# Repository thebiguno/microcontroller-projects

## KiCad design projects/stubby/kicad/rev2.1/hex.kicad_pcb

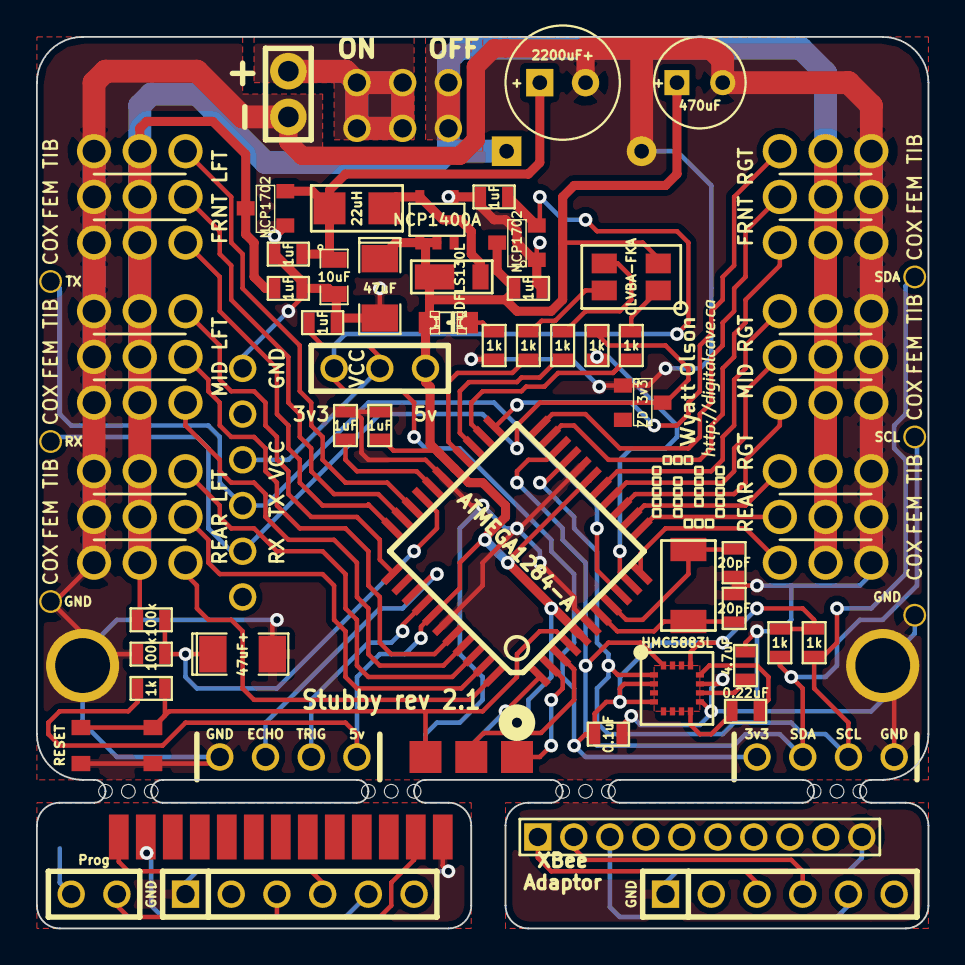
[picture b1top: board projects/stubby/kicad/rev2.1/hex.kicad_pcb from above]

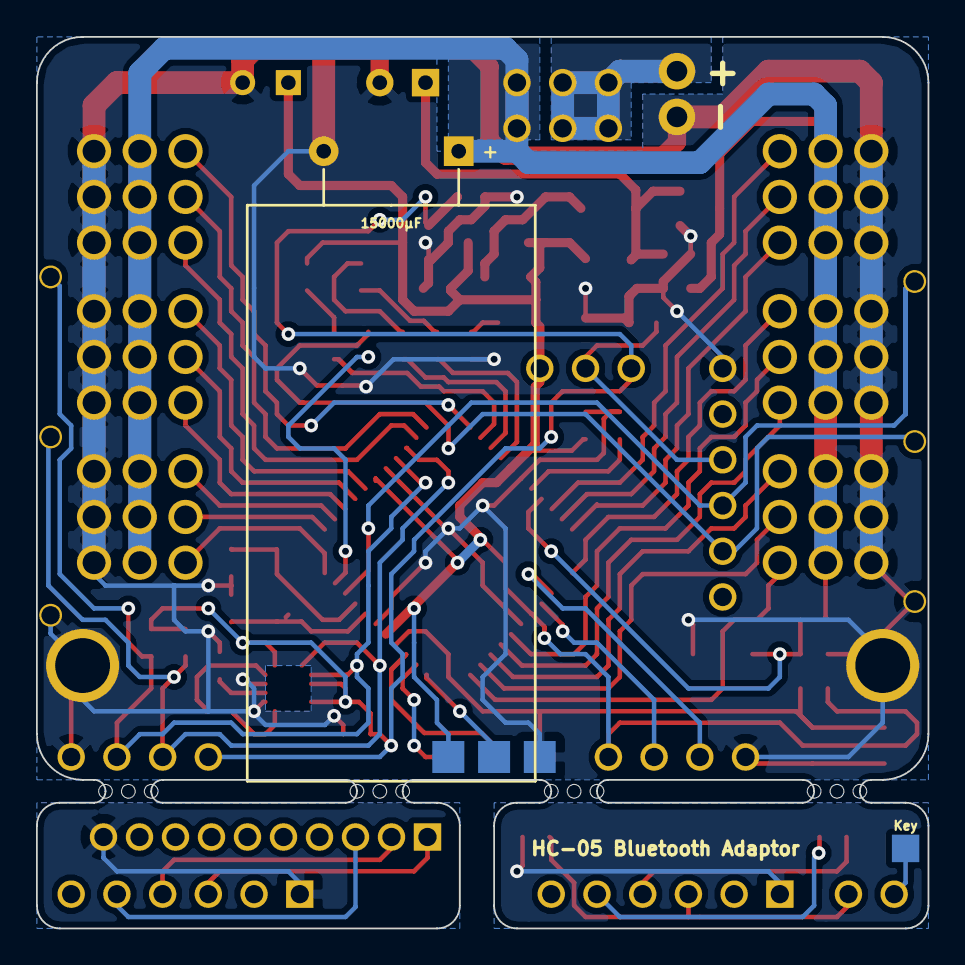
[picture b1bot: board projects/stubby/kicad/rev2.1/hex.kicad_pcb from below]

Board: 2 copper layers, 49.5 x 49.5 mm, 72 parts (2 on the bottom side), 60 nets.

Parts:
1PIN, 1PIN#2, 1PIN#3, 1PIN#4, 1PIN#5, 1PIN#6, 1PIN#7, 1PIN#8: P***; 1pin
C1: 10uF; SM0805
C2: 2200uF+; C1V7
C3, C4, C5, C12, C13, C14, C16: 1uF; SM0603_VALUE
C6: 4.7uF; SM0603_VALUE
C7, C8: 20pF; SM0603_VALUE
C9: 0.22uF; SM0603_VALUE
C10: 47uF; SM1206POL
C11: 470uF; C1V5
C15: 47uF+; SM1206POL
C17: 15000µF; C1V8
C19: 0.1uF; SM0603_VALUE
D1: DFLS130L; POWERDI_123
D2: LED; LED-0805-MARKED_ANODE
D3: CLVBA-FKA; 4-PLCC
IC1: ATMEGA1284-A; TQFP44
JP1: CONN_3; SIL-3
L1: 22uH; SM1007
P1, P2, P11: CONN_6; SIL-6
P3: CONN_10; SIL-10
P4: CONN_13; HC05_Edge
P5, P10: CONN_4; SIL-4
P6: CONN_2; SIL-2
P7: CONN_1; SIL-1
P8: BATT (4.8V-6V); SIL-2
P9: PROG; ISP_EDGE
R1, R2, R3, R4, R7, R8, R9, R10: 1k; SM0603_VALUE
R5, R6: 100k; SM0603_VALUE
S2: FRNT LFT; HEX_LEG
S3: FRNT RGT; HEX_LEG_REVERSE
S4: MID LFT; HEX_LEG
S5: MID RGT; HEX_LEG_REVERSE
S6: REAR LFT; HEX_LEG
S7: REAR RGT; HEX_LEG_REVERSE
SW1: SW_PUSH; sw_42_32
SW2: DPDT
U1: HMC5883L; LPCC-16
VAL: DIGITALCAVE_LOGO_WIDE_SMALL
VR1, VR3: MCP1702; SOT23
VR2: NCP1400A; SOT23-5
X1: CRYSTAL; CRYSTAL_SMD_5x3.2
ZD1: ZD 3v3; SOT23
mouse_bites: VAL**; mouse_bites
mouse_bites#2, mouse_bites#3, mouse_bites#4: VAL**; mouse_bites

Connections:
+3.3V: C13.1, C19.1, JP1.3, P5.1, R1.2, R2.2, U1.2, U1.4, U1.13, VR3.3
+5V: C10.1, C11.1, C12.2, C14.1, D1.2, D2.1, D3.2, IC1.5, IC1.17, IC1.27, IC1.38, JP1.1, P9.2, P10.1, R3.1, VR2.1, VR2.2, VR3.2
+BATT: C4.1, C17.1, R5.1, S2.4, S2.5, S2.6, S3.4, S3.5, S3.6, S4.4, S4.5, S4.6, S5.4, S5.5, S5.6, S6.4, S6.5, S6.6, S7.4, S7.5, S7.6, SW2.3, SW2.6, VR1.2
/ADC_BATTERY_METER: C15.1, IC1.30, R5.2, R6.2
/AREF: C5.2, IC1.29
/AVR_RX: 1PIN#6.1, IC1.9, P11.4
/AVR_TX: IC1.10, R7.1
/BATTERY: P8.1, SW2.1, SW2.2, SW2.4, SW2.5
/BLUETOOTH_GND: P2.1, P4.13
/DIST_ECHO: IC1.36, P10.3
/DIST_TRIG: IC1.37, P10.2
/I2C_SCL: 1PIN#3.1, IC1.19, P5.3, R1.1, U1.1
/I2C_SDA: 1PIN#2.1, IC1.20, P5.2, R2.1, U1.16
/LED_BL: IC1.25, R9.1
/LED_BL_R: D3.3, R9.2
/LED_GR: IC1.26, R8.1
/LED_GR_R: D3.4, R8.2
/LED_RD: IC1.24, R10.1
/LED_RD_R: D3.1, R10.2
/MISO: IC1.2, P9.1
/MODULE_RX: 1PIN#5.1, P11.5, R7.2, ZD1.2
/MOSI: IC1.1, P9.4
/PWM00: IC1.33, S2.1
/PWM01: IC1.32, S2.2
/PWM02: IC1.31, S2.3
/PWM03: IC1.23, S3.1
/PWM04: IC1.22, S3.2
/PWM05: IC1.21, S3.3
/PWM06: IC1.41, S4.1
/PWM07: IC1.40, S4.2
/PWM08: IC1.34, S4.3
/PWM09: IC1.16, S5.1
/PWM10: IC1.15, S5.2
/PWM11: IC1.14, S5.3
/PWM12: IC1.44, S6.1
/PWM13: IC1.43, S6.2
/PWM14: IC1.42, S6.3
/PWM15: IC1.13, S7.1
/PWM16: IC1.12, S7.2
/PWM17: IC1.11, S7.3
/RESET: IC1.4, P9.5, R3.2, SW1.2
/SCK: IC1.3, P9.3
/XBEE_GND: P1.1, P3.10
/XTAL1: C8.2, IC1.8, X1.1
/XTAL2: C7.2, IC1.7, X1.2
GND: 1PIN.1, 1PIN#4.1, 1PIN#7.1, 1PIN#8.1, C1.2, C2.2, C3.2, C4.2, C5.1, C6.2, C7.1, C8.1, C10.2, C11.2, C12.1, C13.2, C14.2, C15.2, C16.1, C17.2, C19.2, IC1.6, IC1.18, IC1.28, IC1.39, P5.4, P8.2, P9.6, P10.4, P11.1, R4.1, R6.1, S2.7, S2.8, S2.9, S3.7, S3.8, S3.9, S4.7, S4.8, S4.9, S5.7, S5.8, S5.9, S6.7, S6.8, S6.9, S7.7, S7.8, S7.9, SW1.1, U1.9, U1.11, VR1.1, VR2.4, VR3.1, ZD1.1
unnamed: P1.5, P3.3
unnamed: P1.4, P3.2
unnamed: P1.3, P3.1
unnamed: P2.5, P4.2
unnamed: P2.4, P4.1
unnamed: P2.3, P4.12, P6.2
unnamed: C16.2, JP1.2, P11.3
unnamed: D1.1, L1.2, VR2.5
unnamed: P6.1, P7.1
unnamed: C9.1, U1.8
unnamed: C9.2, U1.12
unnamed: D2.2, R4.2
unnamed: C6.1, U1.10
unnamed: C1.1, C2.1, C3.1, L1.1, VR1.3

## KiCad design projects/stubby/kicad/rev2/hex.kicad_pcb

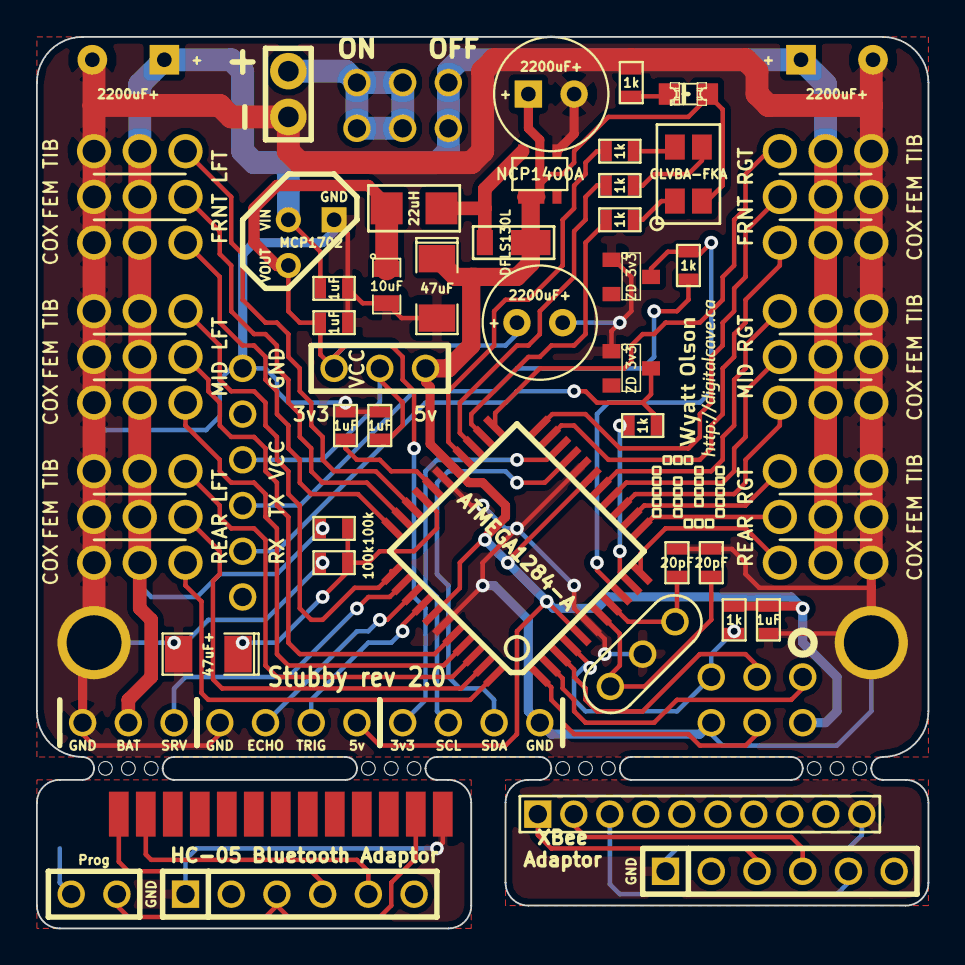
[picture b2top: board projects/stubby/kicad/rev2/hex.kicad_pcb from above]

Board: 2 copper layers, 49.5 x 49.5 mm, 60 parts (1 on the bottom side), 58 nets.

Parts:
1PIN, 1PIN#2: P***; 1pin
C1, C8: 2200uF+; C1V7
C2, C3, C9, C13, C14: 1uF; SM0603_VALUE
C4, C5: 2200uF+; C1V8
C6: 10uF; SM0805
C7: 47uF; SM1206POL
C10: 47uF+; SM1206POL
C11, C12: 20pF; SM0603_VALUE
D1: DFLS130L; POWERDI_123
D2: LED; LED-0805-MARKED_ANODE
D3: CLVBA-FKA; 4-PLCC
IC1: ATMEGA1284-A; TQFP44
JP1: CONN_3; SIL-3
L1: 22uH; SM1007
P1: BATT (4.8V-6V); SIL-2
P2: PROG; ISP
P3: CONN_10; SIL-10
P4, P6, P8: CONN_6; SIL-6
P5: CONN_13; HC05_Edge
P7: CONN_1; SIL-1
P9: CONN_2; SIL-2
P10, P11: CONN_4; SIL-4
R1, R4, R5, R6, R7, R8, R9: 1k; SM0603_VALUE
R2, R3: 100k; SM0603_VALUE
S1: FRNT LFT; HEX_LEG
S2: FRNT RGT; HEX_LEG_REVERSE
S3: MID LFT; HEX_LEG
S4: MID RGT; HEX_LEG_REVERSE
S5: REAR LFT; HEX_LEG
S6: REAR RGT; HEX_LEG_REVERSE
S7: CONN_3; SIL-3
SW1: DPDT
VAL: DIGITALCAVE_LOGO_WIDE_SMALL
VR1: MCP1702; TO92
VR2: NCP1400A; SOT23-5
X1: CRYSTAL_RESONATOR
ZD1, ZD2: ZD 3v3; SOT23
mouse_bites: VAL**; mouse_bites
mouse_bites#2, mouse_bites#3, mouse_bites#4: VAL**; mouse_bites

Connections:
+3.3V: C1.1, C2.1, C6.1, JP1.3, L1.1, P10.1, VR1.3
+5V: C7.1, C8.1, C9.2, D1.2, D2.1, D3.2, IC1.5, IC1.17, IC1.27, IC1.38, JP1.1, P2.2, P11.1, R4.1, VR2.1, VR2.2
+BATT: C3.1, C4.1, C5.1, R2.1, S1.4, S1.5, S1.6, S2.4, S2.5, S2.6, S3.4, S3.5, S3.6, S4.4, S4.5, S4.6, S5.4, S5.5, S5.6, S6.4, S6.5, S6.6, S7.2, SW1.3, SW1.6, VR1.2
/ADC_BATTERY_METER: C10.1, IC1.30, R2.2, R3.2
/AREF: C13.2, IC1.29
/AVR_RX: IC1.9, R9.1, ZD1.2
/AVR_TX: IC1.10, R8.1
/BATTERY: P1.1, SW1.1, SW1.2, SW1.4, SW1.5
/BLUETOOTH_GND: P5.13, P8.1
/DIST_ECHO: IC1.36, P11.3
/DIST_SERVO: IC1.35, S7.3
/DIST_TRIG: IC1.37, P11.2
/I2C_SCL: IC1.19, P10.3
/I2C_SDA: IC1.20, P10.2
/LED_BL: IC1.25, R6.1
/LED_BL_R: D3.3, R6.2
/LED_GR: IC1.26, R5.1
/LED_GR_R: D3.4, R5.2
/LED_RD: IC1.24, R7.1
/LED_RD_R: D3.1, R7.2
/MISO: IC1.2, P2.1
/MOSI: IC1.1, P2.4
/PWM00: IC1.33, S1.1
/PWM01: IC1.32, S1.2
/PWM02: IC1.31, S1.3
/PWM03: IC1.23, S2.1
/PWM04: IC1.22, S2.2
/PWM05: IC1.21, S2.3
/PWM06: IC1.41, S3.1
/PWM07: IC1.40, S3.2
/PWM08: IC1.34, S3.3
/PWM09: IC1.16, S4.1
/PWM10: IC1.15, S4.2
/PWM11: IC1.14, S4.3
/PWM12: IC1.44, S5.1
/PWM13: IC1.43, S5.2
/PWM14: IC1.42, S5.3
/PWM15: IC1.13, S6.1
/PWM16: IC1.12, S6.2
/PWM17: IC1.11, S6.3
/RESET: IC1.4, P2.5, R4.2
/SCK: IC1.3, P2.3
/XBEE_GND: P3.10, P4.1
/XTAL1: C12.2, IC1.8, X1.1
/XTAL2: C11.2, IC1.7, X1.2
GND: 1PIN.1, 1PIN#2.1, C1.2, C2.2, C3.2, C4.2, C5.2, C6.2, C7.2, C8.2, C9.1, C10.2, C11.1, C12.1, C13.1, C14.1, IC1.6, IC1.18, IC1.28, IC1.39, P1.2, P2.6, P6.1, P10.4, P11.4, R1.2, R3.1, S1.7, S1.8, S1.9, S2.7, S2.8, S2.9, S3.7, S3.8, S3.9, S4.7, S4.8, S4.9, S5.7, S5.8, S5.9, S6.7, S6.8, S6.9, S7.1, VR1.1, VR2.4, X1.3, ZD1.1, ZD2.1
unnamed: P5.2, P8.5
unnamed: P5.1, P8.4
unnamed: P3.3, P4.5
unnamed: D1.1, L1.2, VR2.5
unnamed: P7.1, P9.1
unnamed: P5.12, P8.3, P9.2
unnamed: P3.2, P4.4
unnamed: P3.1, P4.3
unnamed: P6.4, R9.2
unnamed: P6.5, R8.2, ZD2.2
unnamed: C14.2, JP1.2, P6.3
unnamed: D2.2, R1.1

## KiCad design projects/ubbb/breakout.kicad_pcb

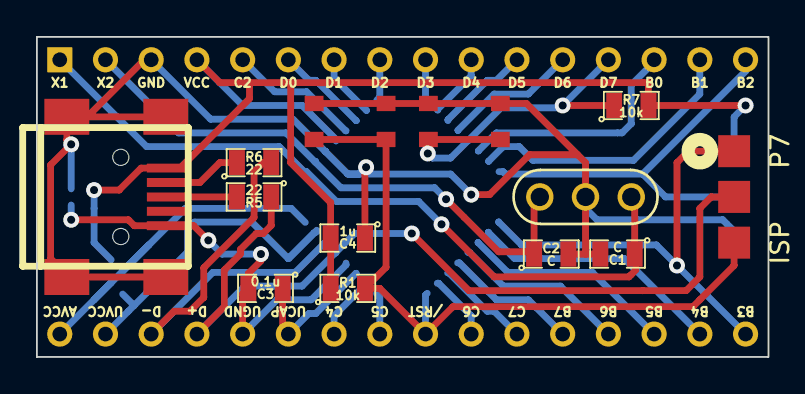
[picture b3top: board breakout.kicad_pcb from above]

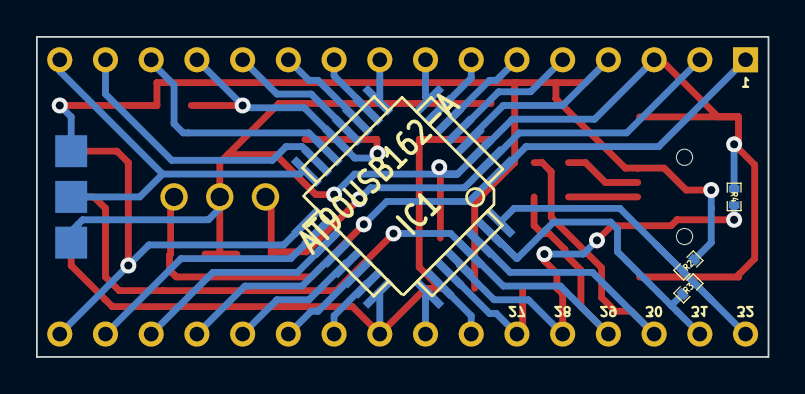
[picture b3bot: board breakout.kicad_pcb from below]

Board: 2 copper layers, 40.6 x 17.8 mm, 21 parts (4 on the bottom side), 34 nets.

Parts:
C1, C2: C; SM0805
C3: 0.1u; SM0805
C4: 1u; SM0805
CON1: USB-MINI-B; USB_MINI_B_fixed
IC1: AT90USB162-A; TQFP32
P2, P3, P4, P5: CONN_8; SIL-8
P7: ISP; ISP_EDGE
R1, R7: 10k; SM0805
R2, R3, R4: 0; SM0402_r
R5, R6: 22; SM0805
SW1, SW2: SW_PUSH_SMALL; sw_42_32
X1: CRYSTAL_RESONATOR

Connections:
/a1: C1.1, IC1.1, P2.1, X1.1
/a2: C2.1, IC1.2, P2.2, X1.2
/a4: C4.2, CON1.1, IC1.4, P2.4, P7.2, R1.1, R2.1, R7.2
/a5: IC1.5, P2.5
/a6: IC1.6, P2.6
/a7: IC1.7, P2.7
/a8: IC1.8, P2.8
/a9: IC1.9, P3.1
/a10: IC1.10, P3.2
/a11: IC1.11, P3.3
/a12: IC1.12, P3.4
/a13: IC1.13, P3.5, R7.1, SW2.2
/a14: IC1.14, P3.6
/a15: IC1.15, P3.7
/a16: IC1.16, P3.8, P7.4
/a17: IC1.17, P4.1, P7.1
/a18: IC1.18, P4.2
/a19: IC1.19, P4.3
/a20: IC1.20, P4.4
/a21: IC1.21, P4.5
/a22: IC1.22, P4.6
/a23: IC1.23, P4.7
/a24: IC1.24, P4.8, P7.5, R1.2, SW1.2
/a25: IC1.25, P5.1
/a26: IC1.26, P5.2
/a27: C3.1, IC1.27, P5.3
/a28: C3.2, CON1.5, IC1.28, P5.4, R4.2
/a29: IC1.29, P5.5, P7.3, R5.1
/a30: IC1.30, P5.6, R6.2
/a31: IC1.31, P5.7, R3.1
/a32: IC1.32, P5.8, R2.2, R3.2
GND: C1.2, C2.2, C4.1, CON1.6, CON1.7, CON1.8, CON1.9, IC1.3, P2.3, P7.6, R4.1, SW1.1, SW2.1, X1.3
unnamed: CON1.2, R6.1
unnamed: CON1.3, R5.2

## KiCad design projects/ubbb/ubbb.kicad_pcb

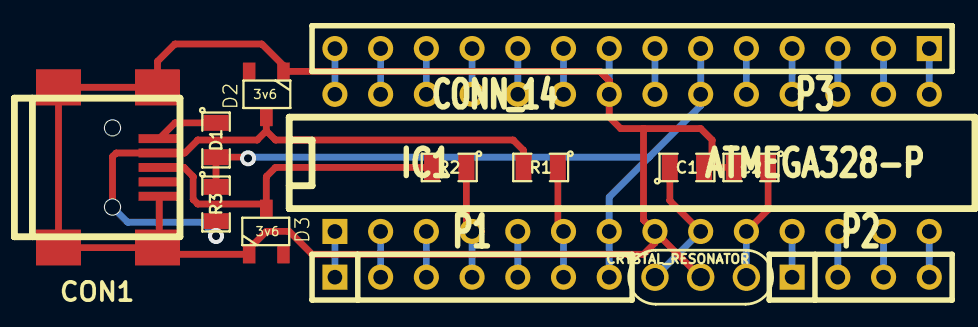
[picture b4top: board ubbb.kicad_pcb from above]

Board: 2 copper layers, 14 parts (0 on the bottom side), 29 nets.

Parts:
C1, C2: 20pF; SM0805
CON1: USB-MINI-B; USB_MINI_B
D1: DIODE; SM0805
D2, D3: 3v6; SOT23
IC1: ATMEGA328-P; DIP-28__300
P1: CONN_7; SIL-7
P2: CONN_4; SIL-4
P3: CONN_14; SIL-14
R1, R2: 68; SM0805
R3: R; SM0805
X1: CRYSTAL_RESONATOR

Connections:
/1: IC1.1, P1.1
/2: IC1.2, P1.2
/3: IC1.3, P1.3
/4: IC1.4, P1.4, R2.1
/5: IC1.5, P1.5
/6: IC1.6, P1.6, R1.1
/9: C1.1, IC1.9, X1.1
/10: C2.1, IC1.10, X1.2
/11: IC1.11, P2.1
/12: IC1.12, P2.2
/13: IC1.13, P2.3
/14: IC1.14, P2.4
/15: IC1.15, P3.1
/16: IC1.16, P3.2
/17: IC1.17, P3.3
/18: IC1.18, P3.4
/19: IC1.19, P3.5
/21: IC1.21, P3.7
/23: IC1.23, P3.9
/24: IC1.24, P3.10
/25: IC1.25, P3.11
/26: IC1.26, P3.12
/27: IC1.27, P3.13
/28: IC1.28, P3.14
/D+: CON1.3, D3.2, R2.2
/D-: CON1.2, D2.2, R1.2, R3.2
/VBUS: CON1.1, D1.1
GND: C1.2, C2.2, CON1.5, CON1.6, CON1.7, CON1.8, CON1.9, D2.1, D3.1, IC1.8, IC1.22, P3.8, X1.3
VCC: D1.2, IC1.7, IC1.20, P1.7, P3.6, R3.1

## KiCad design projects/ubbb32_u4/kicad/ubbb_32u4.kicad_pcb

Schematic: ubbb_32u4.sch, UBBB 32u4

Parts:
C1, C2: 8pF
C3, C5, C6, C7, C8, C9: 0.1uF
C4: 1uF
CON1: USB-MINI-B
D1: RGB_LED_COMMON_ANODE_ALT1
D2: TVS; SOT23; Digikey Part# 568-4676-1-ND
K1: PINS_4
MP1: MOUNTING_HOLE
P1: ISP
P2, P3, P4, P5, P6, P7: CONN_5
R1, R2: 22
R3, R4, R5, R6, R7: 1k
R8: 0
SW1, SW2: SW_PUSH_SMALL
U1: ATMEGA32U4-A; TQFP44
X1: CRYSTAL_SMD_4PIN

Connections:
+5V: C5.2, C6.2, C7.2, C8.2, C9.2, D1.1, P1.2, P2.2, R3.1, R7.2, R8.2, U1.2, U1.14, U1.24, U1.34, U1.44
/AREF: C3.1, P2.3, U1.42
/B0: P7.5, U1.8
/B1: P1.3, P7.4, U1.9
/B2: P1.4, P7.3, U1.10
/B3: P1.1, P7.2, U1.11
/B4: P5.1, R4.2, U1.28
/B5: P4.5, R5.2, U1.29
/B6: P4.4, R6.2, U1.30
/B7: P7.1, U1.12
/C6: P4.3, U1.31
/C7: P4.2, U1.32
/D0: D2.1, P6.4, U1.18
/D1: D2.2, P6.3, U1.19
/D2: P6.2, U1.20
/D3: P6.1, U1.21
/D4: P5.5, U1.25
/D5: P5.4, U1.22
/D6: P5.3, U1.26
/D7: P5.2, U1.27
/D+: CON1.3, K1.2, R1.1
/D-: CON1.2, K1.3, R2.1
/E2: P4.1, R7.1, SW2.1, U1.33
/E6: P2.4, U1.1
/F0: P2.5, U1.41
/F1: P3.1, U1.40
/F4: P3.2, U1.39
/F5: P3.3, U1.38
/F6: P3.4, U1.37
/F7: P3.5, U1.36
/LB: D1.3, R5.1
/LG: D1.4, R6.1
/LR: D1.2, R4.1
/RESET: P1.5, P6.5, R3.2, SW1.2, U1.13
/UCAP: C4.1, U1.6
/VBUS: CON1.1, K1.4, R8.1, U1.7
GND: C1.1, C2.1, C3.2, C4.2, C5.1, C6.1, C7.1, C8.1, C9.1, CON1.5, CON1.6, CON1.7, CON1.8, CON1.9, D2.3, K1.1, MP1.1, P1.6, P2.1, SW1.1, SW2.2, U1.5, U1.15, U1.23, U1.35, U1.43, X1.2, X1.4
unnamed: C2.2, U1.16, X1.1
unnamed: C1.2, U1.17, X1.3
unnamed: R1.2, U1.4
unnamed: R2.2, U1.3

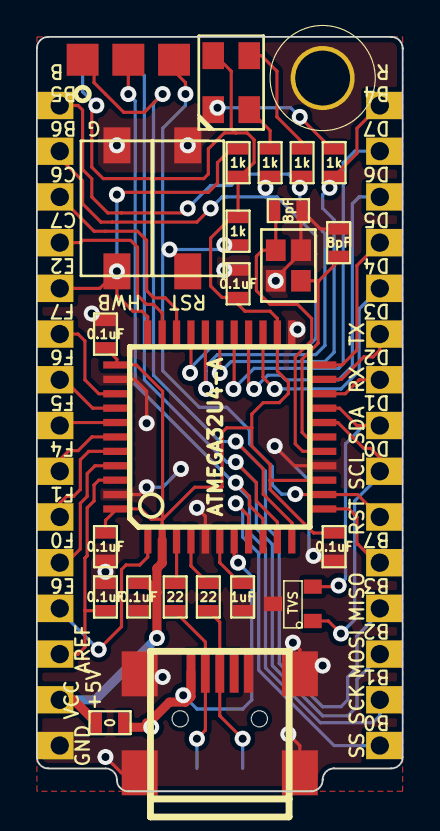
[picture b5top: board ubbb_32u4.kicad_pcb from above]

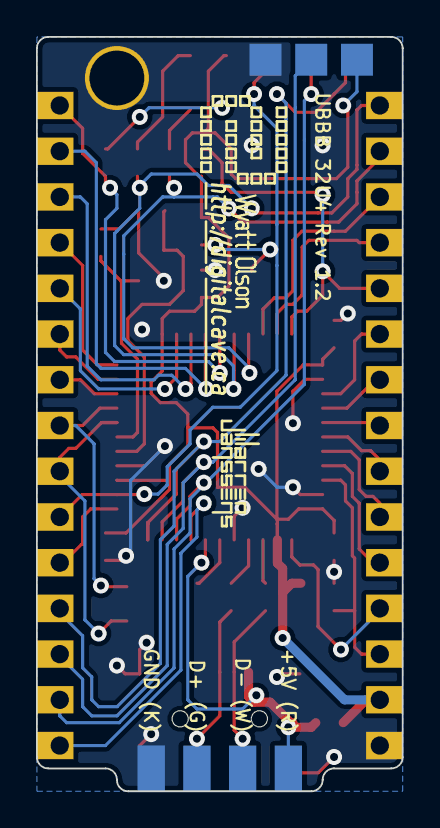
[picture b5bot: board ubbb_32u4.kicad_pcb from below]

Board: 2 copper layers, 20.3 x 41.9 mm, 37 parts (5 on the bottom side), 41 nets.

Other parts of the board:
DIGITALCAVE_URL: VAL**; DIGITALCAVE_URL
VAL: REF; DIGITALCAVE_LOGO
VAL#2: DIGITALCAVE_AUTHOR
WJ10: VAL**; WJ10
